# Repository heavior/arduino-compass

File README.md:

# arduino-compass
Working Jack Sparrow Compass

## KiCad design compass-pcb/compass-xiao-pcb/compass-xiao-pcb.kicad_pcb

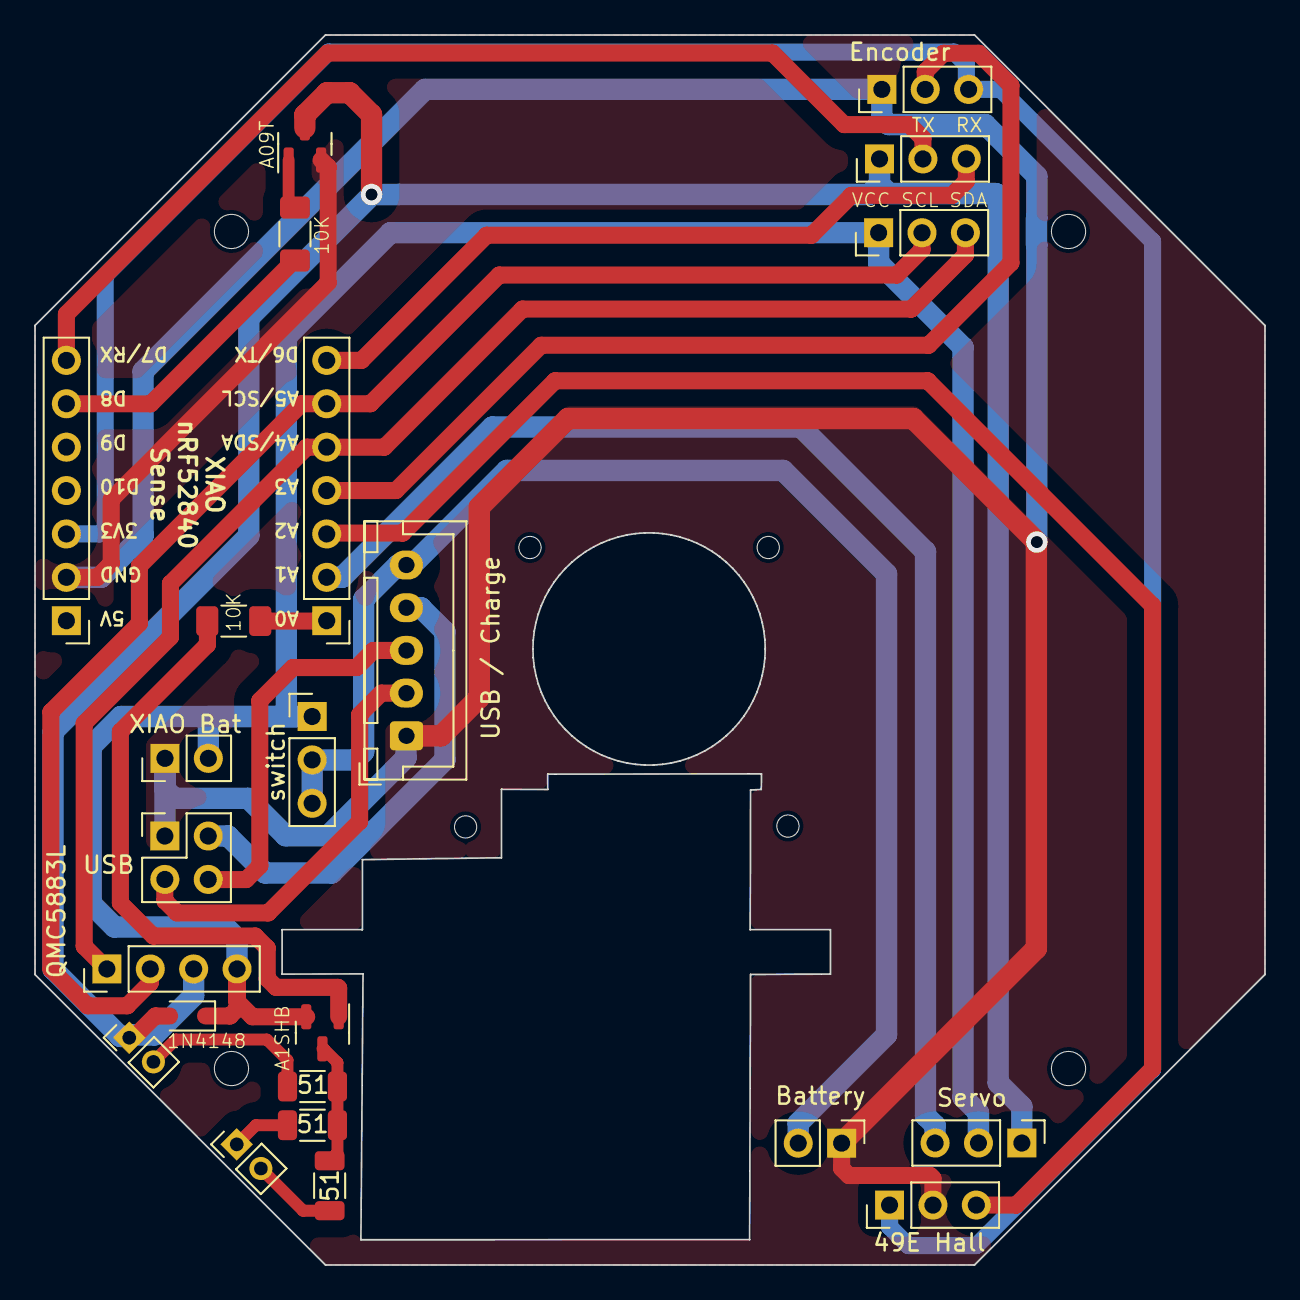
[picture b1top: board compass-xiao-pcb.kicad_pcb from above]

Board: 2 copper layers, 72.0 x 72.0 mm, 16 parts (0 on the bottom side), 4 nets.

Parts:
1N4148: D_SOD-323
10K, 10K#2: R1002; R_1206_3216Metric_Pad1.30x1.75mm_HandSolder
49E Hall: PinHeader_1x03_P2.54mm_Vertical
51, 51#2, 51#3: R_1206_3216Metric
A1SHB, A09T: SOT-23
Battery: PinHeader_1x02_P2.54mm_Vertical
QMC5883L: PinHeader_1x04_P2.54mm_Vertical
Servo: PinHeader_1x03_P2.54mm_Vertical
USB: PinHeader_2x02_P2.54mm_Vertical
USB / Charge: JST_XH_B5B-XH-A_1x05_P2.50mm_Vertical
XIAO Bat: PinHeader_1x02_P2.54mm_Vertical
switch: PinHeader_1x03_P2.54mm_Vertical

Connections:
3.7V: 1N4148.1, A1SHB.2, QMC5883L.4, Servo.2, XIAO Bat.2
BAT: Battery.2, USB / Charge.5
GND: 49E Hall.2, A09T.2, Battery.1, USB / Charge.1, XIAO Bat.1
NEG: 1N4148.2, A09T.3, QMC5883L.3, Servo.1

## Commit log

2023-04-11 Create main.ino
    Initial commit for the arduino sketch
2023-04-11 Update main.ino
    Code structure, some chatGPT contributions, lots of TODOs
2023-04-14 Compass calibration code
2023-04-14 disable not compiling code
2023-04-15 Led indicator library
2023-04-15 calibrate tool logic
2023-04-15 comments for calibration library
2023-04-21 plugging compass lib to main, fixing motor direction, adding hall sensor to shut down the motor
2023-05-07 support for tested layout and rev2 board + battery level
2023-05-07 pcb outlines
2023-05-07 adding comments to psb
2023-05-07 adding battery jumper
2023-05-07 minor improvements in debug output
2023-05-07 playing with placing main switch on the board
2023-05-07 Revert "playing with placing main switch on the board"
    This reverts commit f90624a9c38ec8366b61e906c035f362712ec212.
2023-05-07 Update Compass.kicad_pcb
    moving battery jumper
2023-05-07 adding spacing for ground connectors
2023-05-07 adding alignment anchors
2023-05-07 comments for anchors
2023-05-07 polishing
2023-05-09 Polishing pcb design
2023-05-09 fixing USB contacts to be one-sided
2023-05-09 Update Compass.kicad_pcb
    fixed error in hall sensor position
2023-05-09 fixing mount holes
2023-05-09 Larger through holes
2023-05-09 bigger pads for holes where possible, additional support under Arduino
2023-05-09 adding soldering support for back side of arduino
2023-05-09 expanding footprint for small dots where possible
2023-05-09 polishing layout
2023-05-09 moving jumpers for more space
2023-05-15 moving main switch to the board
2023-05-15 tons of debug
2023-05-15 moving charger to the board
2023-05-15 polishing the pcb
2023-05-15 copy main shape to back side
2023-05-16 polishing, adding border
2023-05-16 pcb border (shape)
2023-05-16 mounting holes for the servo mount
2023-05-16 condence power lines
2023-05-16 ground on arduino
2023-05-16 using pin pads everywhere
2023-05-16 sensor tracking
2023-05-16 ground USB connector to save space
2023-05-16 moving USB and charging ports a bit
2023-05-16 larger mounting holes
2023-05-20 fixes for pcb
2023-05-20 Compass calibration for different dial positions
2023-05-20 Polishing pcb, adding spare i2c and 3.3 points
2023-05-21 working with real coordinates + spinning effect
2023-05-21 minor board fixes
2023-05-21 some cleanup
2023-05-21 Bluetooth service to calibrate compass
2023-05-21 polishing calibration logic
2023-05-21 Jack Sparrow Easter Egg
2023-05-24 fixes for animation, drafting future logic for direction accounting for accuracy
2023-05-24 adding characteristic to control calibration - one angle at a time
2023-05-24 Fixing reading calibration settings from BT host
2023-05-24 Sending calibration angle from web page to compass
2023-05-31 Calibration logic fixes
2023-05-31 New calibration logic (untested)
2023-05-31 calibration fixes
2023-06-01 calibrated compass
2023-06-01 Adding standard service for battery level (no idea what for)
2023-06-01 Refactoring compass state
2023-06-01 Sending compass state over BT
2023-06-01 Current calibration to state
2023-06-01 method to use closest calibration instead of interpolation
2023-06-01 CompassConfig for all debug parameters
2023-06-01 restoring prod values
2023-06-02 Mounting holes on the PCB
2023-06-05 pcb - optimizing moto cutout
2023-06-05 fixes for conflicting BT services
2023-06-05 hotfix
2023-06-05 Adding protobuffer for compass config
2023-06-05 Trying to move compass state to use protobuf (Fails at reading in js)
2023-06-05 fixed data transfer
2023-06-05 initialise compassState to force it to send all data in a message
2023-06-06 hotfix for settings
2023-06-06 Transitioning all compass features to one service with protobuf
2023-06-06 fixing calibration web app
2023-06-06 connect/disconnect state for the page
2023-06-06 fixing calibration logic - move dial back if needed
2023-06-06 new calibration
2023-06-07 hotfix for closed lid logic
2023-06-07 data structure for points on the map
2023-06-07 adding location size (radius)
2023-06-07 setting destination as structure
2023-06-07 Account for destination radius when reaching the destination
2023-06-07 Route logic: navigate to closest unvisited destination
2023-06-07 Adding Youtopia points
2023-06-08 random fixes
2023-06-08 moving index.html, trying github pages
2023-06-08 fixing github pages
2023-06-09 YOUtopia fix: do not mark object as visited when lid is closed.
2023-06-16 cleanup
2023-06-16 moving out hardware-dependent motor logic
2023-06-16 rearranging PINs
2023-06-16 fork for compass library
2023-06-16 Moved Sensors hardware dependency from main
2023-06-16 cleanup calibration logic, not going to use it
2023-06-17 debug motor function
2023-06-17 Motor self-calibration
2023-06-17 Fix compass initialization
2023-06-17 Sleep/wakeup logic for motor
2023-06-17 rename motor speed + add UV LED control (needs test)
2023-06-17 fixing time calculation for LED
2023-06-17 first try at storage functions
2023-06-17 small fix for happy dance
2023-06-18 refactoring destinations
2023-06-18 fix read/write file logic
2023-06-18 fixing reading from memory
2023-06-18 Saving visited state to memory
2023-06-18 fixing readin long numbers
2023-06-18 XIAO charging logic
2023-06-18 fix for reading battery level while charging
2023-06-18 moving encoder to Motor.h
2023-06-18 Power switch enabling logic
2023-06-19 Add reading temperature
2023-06-19 motor calibration logic
2023-06-20 Starting new pcb
2023-06-20 calibration: preserve working state
2023-06-20 motor calibration cleanup
2023-06-20 optimizing calibration
2023-06-23 adding clean XIAO pcb
2023-06-23 xiao pcb - all components, no wires
2023-06-23 First iteration of wiring
2023-06-23 added main power mosfet
2023-06-23 Fixing main power line
2023-06-23 minor improvements
2023-06-24 added LED connection points
2023-06-24 more room for servo connector
2023-06-24 minor polishing
2023-06-24 ignore backups
2023-06-24 different mounting holes
2023-06-24 smaller board
2023-06-24 removing large board
2023-06-24 added large USB/charging port
2023-06-25 Fixing LED wire, removing some zones
2023-06-25 fixing cuts and layers
2023-06-25 fixing zones around mounting holes
2023-06-25 corner alignment points
2023-06-25 mounting holes for motor
2023-06-25 USB pads
2023-06-25 fixing ground
2023-06-30 lots of pcb fixes
2023-06-30 optimizing for cricut
2023-06-30 more polishing
2023-07-01 Switching to DFRobot_QMC5883
2023-07-01 motor - debugging
2023-07-01 fixes for PCB pinout
2023-07-01 fixing SCL/SDA connection to compass
2023-07-01 minor debug fix
2023-07-01 going back to software i2c due to wiring mistake
2023-07-01 bunch of fixes
2023-07-01 reducing debug noise from motor
2023-07-02 using named ON/OFF signals to adapt to different MOSFET transistors
2023-07-02 setting default speed when calibration is disabled
2023-07-02 disabling UV LED on start (for default-on mosfet)
2023-07-02 New model with n-channel mosfet for improved power management
2023-07-02 some pcb polishing
2023-07-03 prepping for printing - using mounting holes where possible
2023-07-03 naming nets
2023-07-03 more net naming
2023-07-03 more fixes before printing
2023-07-03 minor fixes, removing filled area
2023-07-04 reducing pcb size to accomodate spacers on the sides
2023-07-04 removing filled area
2023-07-04 precise alignment for the border
2023-07-04 aligning corner mounting points
2023-07-04 fixing wire for new mounting points
2023-07-04 removing noise pads
2023-07-04 fixing wiring for new hole position
2023-07-04 minor wiring fix
2023-07-04 moving mounting hole a bit
2023-07-04 fixing elements positions for new holes
2023-07-04 DRC fixes
2023-07-04 fixing last DRC errors
2023-07-04 last touch for today
2023-07-04 Compass dial svg
2023-07-06 PSB order version
